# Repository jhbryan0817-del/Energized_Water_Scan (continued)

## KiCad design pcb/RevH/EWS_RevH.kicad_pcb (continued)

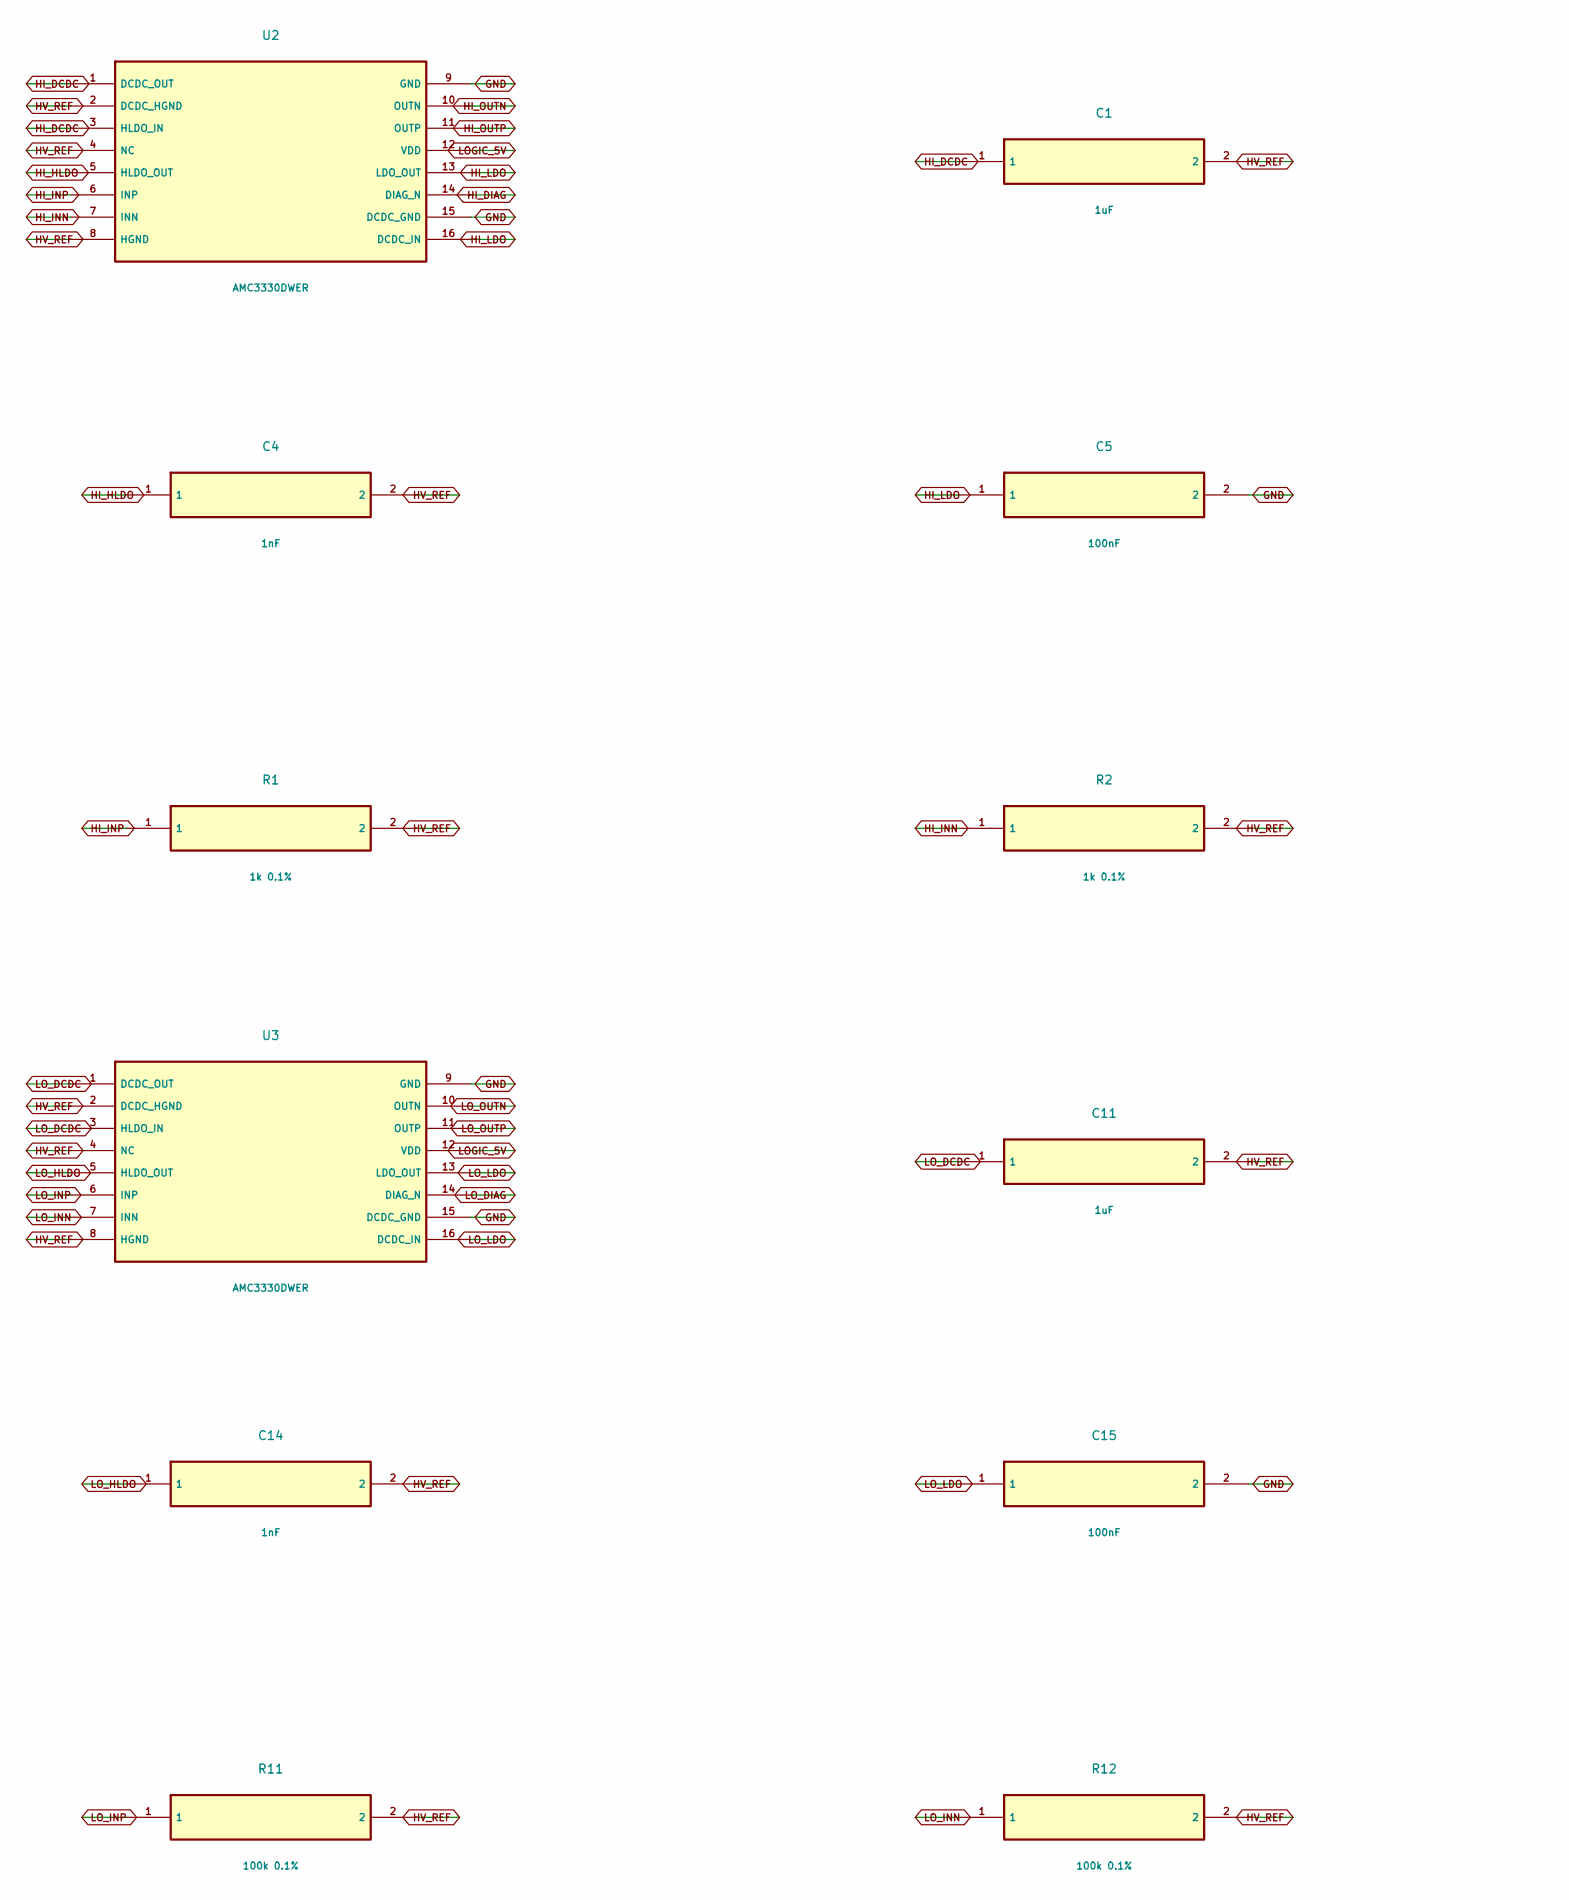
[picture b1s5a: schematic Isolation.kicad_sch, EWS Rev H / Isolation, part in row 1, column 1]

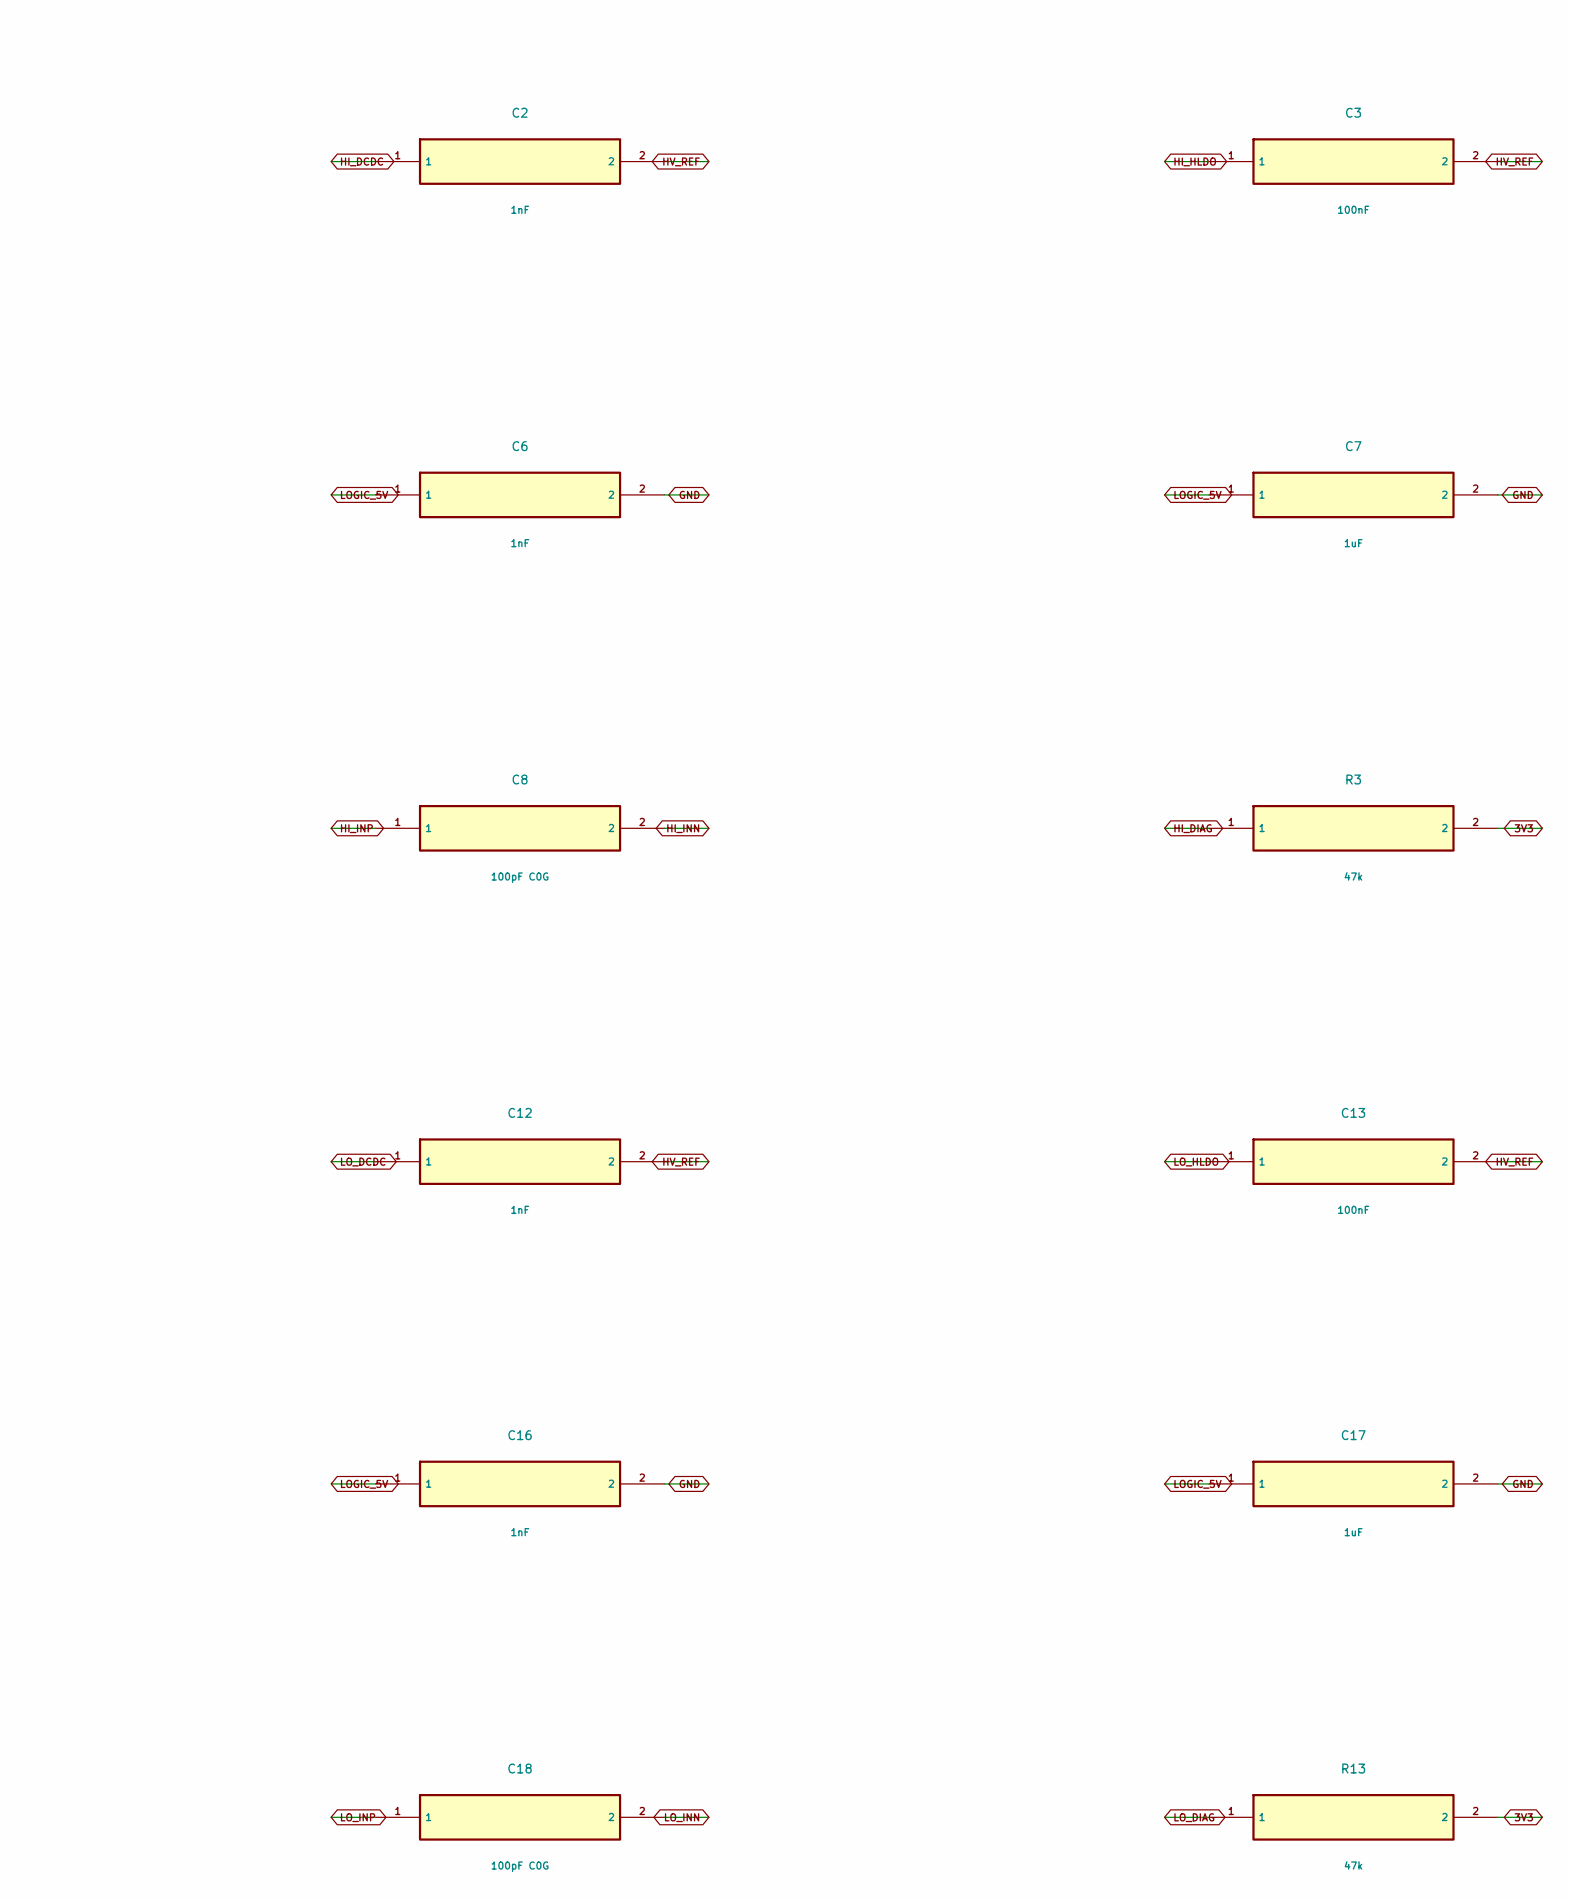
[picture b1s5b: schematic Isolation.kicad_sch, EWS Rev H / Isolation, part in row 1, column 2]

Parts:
C1: 1uF; C1
C2: 1nF; C2
C3: 100nF; C3
C4: 1nF; C4
C5: 100nF; C5
C6: 1nF; C6
C7: 1uF; C7
C8: 100pF C0G; C8
C11: 1uF; C11
C12: 1nF; C12
C13: 100nF; C13
C14: 1nF; C14
C15: 100nF; C15
C16: 1nF; C16
C17: 1uF; C17
C18: 100pF C0G; C18
R1: 1k 0.1%; R1
R2: 1k 0.1%; R2
R3: 47k; R3
R11: 100k 0.1%; R11
R12: 100k 0.1%; R12
R13: 47k; R13
U2: AMC3330DWER; U2
U3: AMC3330DWER; U3

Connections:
3V3: R3.2, R13.2; also elsewhere on the board
GND: C5.2, C6.2, C7.2, C15.2, C16.2, C17.2, U2.9 (GND), U2.15 (DCDC_GND), U3.9 (GND), U3.15 (DCDC_GND); also elsewhere on the board
HI_DCDC: C1.1, C2.1, U2.1 (DCDC_OUT), U2.3 (HLDO_IN)
HI_DIAG: R3.1, U2.14 (DIAG_N); also elsewhere on the board
HI_HLDO: C3.1, C4.1, U2.5 (HLDO_OUT)
HI_INN: C8.2, R2.1, U2.7 (INN); also elsewhere on the board
HI_INP: C8.1, R1.1, U2.6 (INP); also elsewhere on the board
HI_LDO: C5.1, U2.13 (LDO_OUT), U2.16 (DCDC_IN)
HI_OUTN: U2.10 (OUTN); also elsewhere on the board
HI_OUTP: U2.11 (OUTP); also elsewhere on the board
HV_REF: C1.2, C2.2, C3.2, C4.2, C11.2, C12.2, C13.2, C14.2, R1.2, R2.2, R11.2, R12.2, U2.2 (DCDC_HGND), U2.4 (NC), U2.8 (HGND), U3.2 (DCDC_HGND), U3.4 (NC), U3.8 (HGND); also elsewhere on the board
LOGIC_5V: C6.1, C7.1, C16.1, C17.1, U2.12 (VDD), U3.12 (VDD); also elsewhere on the board
LO_DCDC: C11.1, C12.1, U3.1 (DCDC_OUT), U3.3 (HLDO_IN)
LO_DIAG: R13.1, U3.14 (DIAG_N); also elsewhere on the board
LO_HLDO: C13.1, C14.1, U3.5 (HLDO_OUT)
LO_INN: C18.2, R12.1, U3.7 (INN); also elsewhere on the board
LO_INP: C18.1, R11.1, U3.6 (INP); also elsewhere on the board
LO_LDO: C15.1, U3.13 (LDO_OUT), U3.16 (DCDC_IN)
LO_OUTN: U3.10 (OUTN); also elsewhere on the board
LO_OUTP: U3.11 (OUTP); also elsewhere on the board

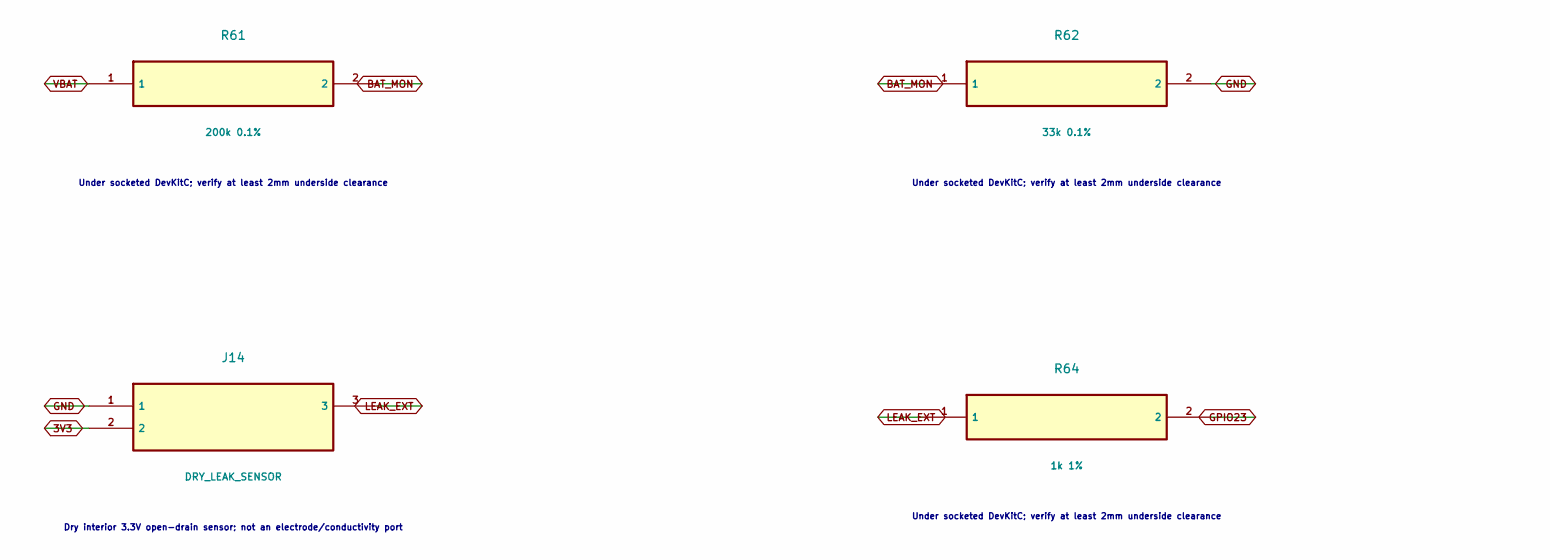
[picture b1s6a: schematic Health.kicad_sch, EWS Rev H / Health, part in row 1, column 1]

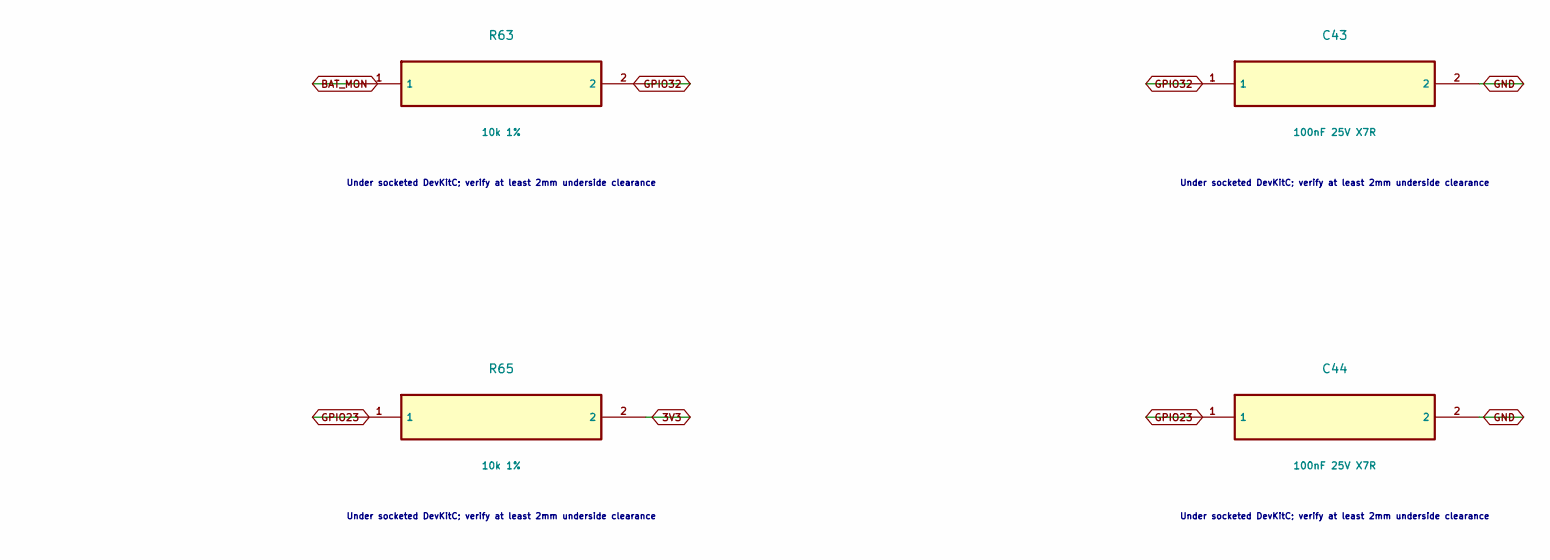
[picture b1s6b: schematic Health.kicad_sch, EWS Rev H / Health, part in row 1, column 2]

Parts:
C43: 100nF 25V X7R; C43
C44: 100nF 25V X7R; C44
J14: DRY_LEAK_SENSOR; J14
R61: 200k 0.1%; R61
R62: 33k 0.1%; R62
R63: 10k 1%; R63
R64: 1k 1%; R64
R65: 10k 1%; R65

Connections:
3V3: J14.2, R65.2; also elsewhere on the board
BAT_MON: R61.2, R62.1, R63.1
GND: C43.2, C44.2, J14.1, R62.2; also elsewhere on the board
GPIO23: C44.1, R64.2, R65.1; also elsewhere on the board
GPIO32: C43.1, R63.2; also elsewhere on the board
LEAK_EXT: J14.3, R64.1
VBAT: R61.1; also elsewhere on the board

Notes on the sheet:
Under socketed DevKitC; verify at least 2mm underside clearance
Dry interior 3.3V open-drain sensor; not an electrode/conductivity port

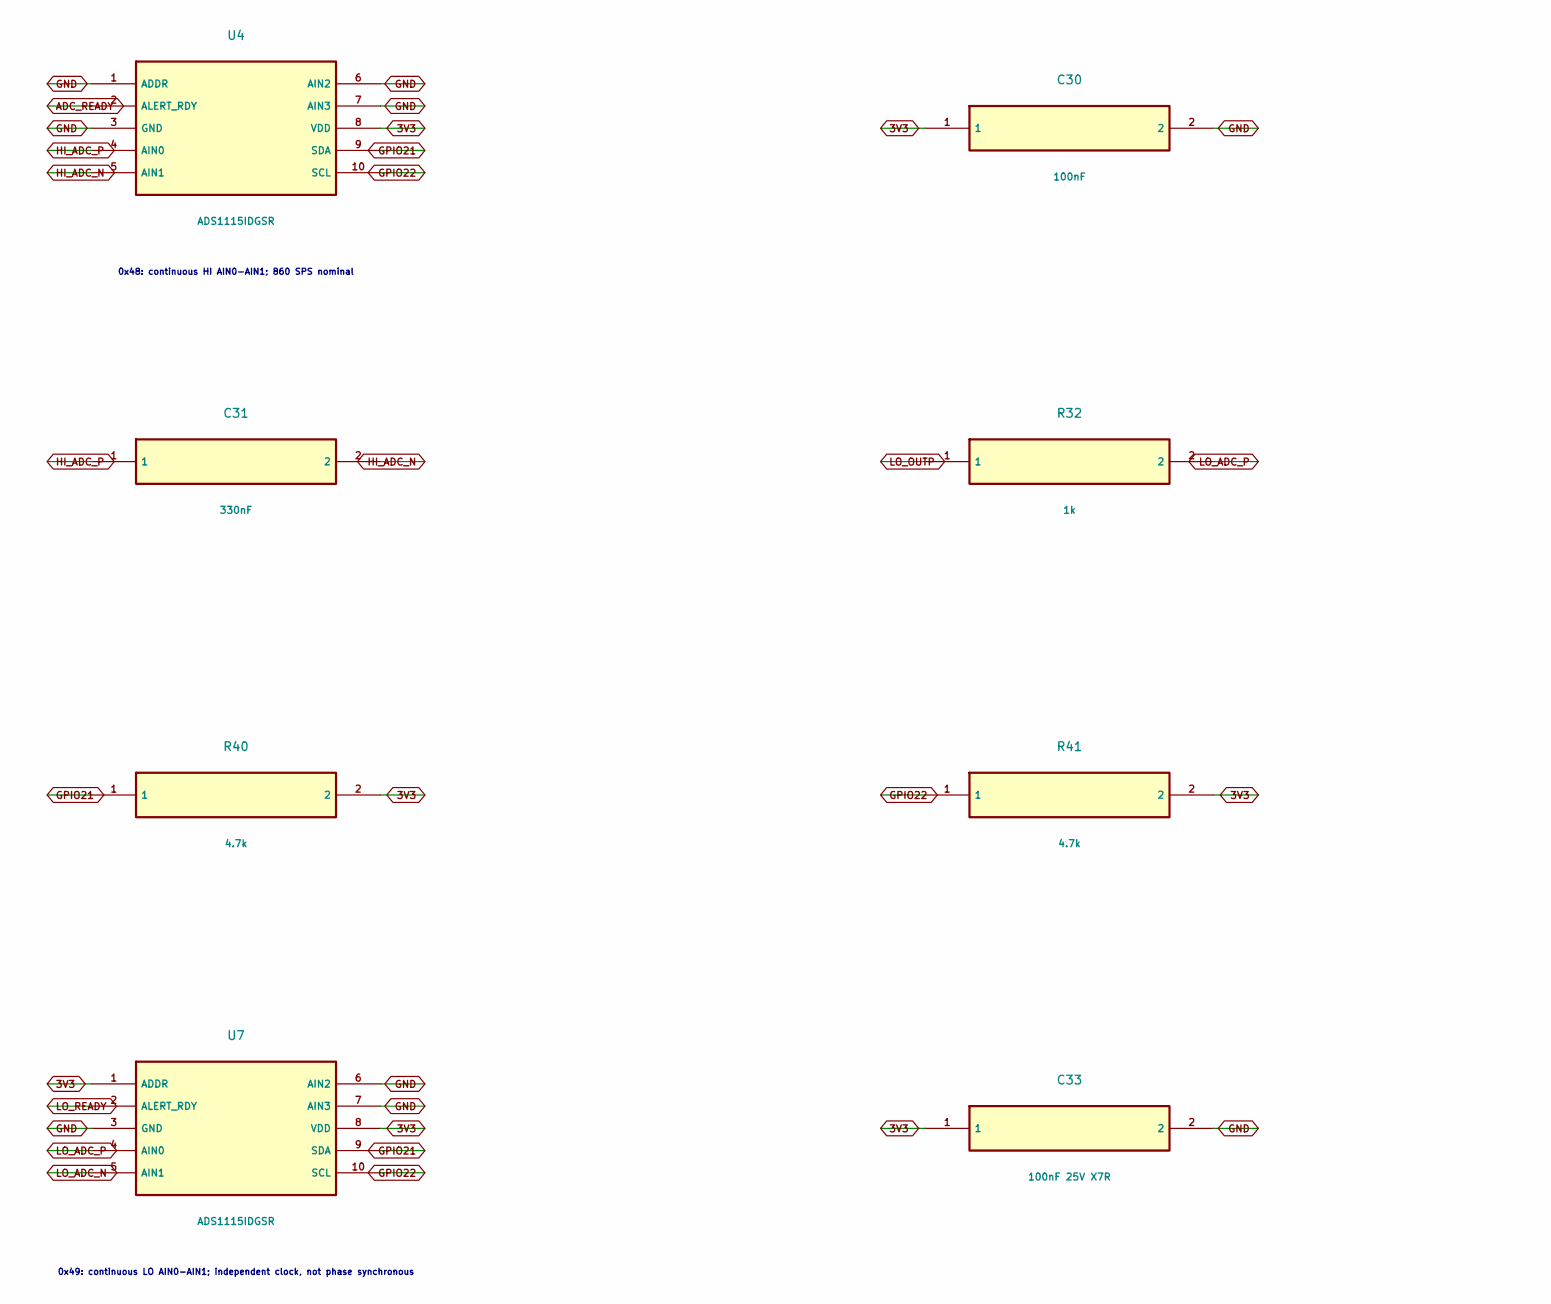
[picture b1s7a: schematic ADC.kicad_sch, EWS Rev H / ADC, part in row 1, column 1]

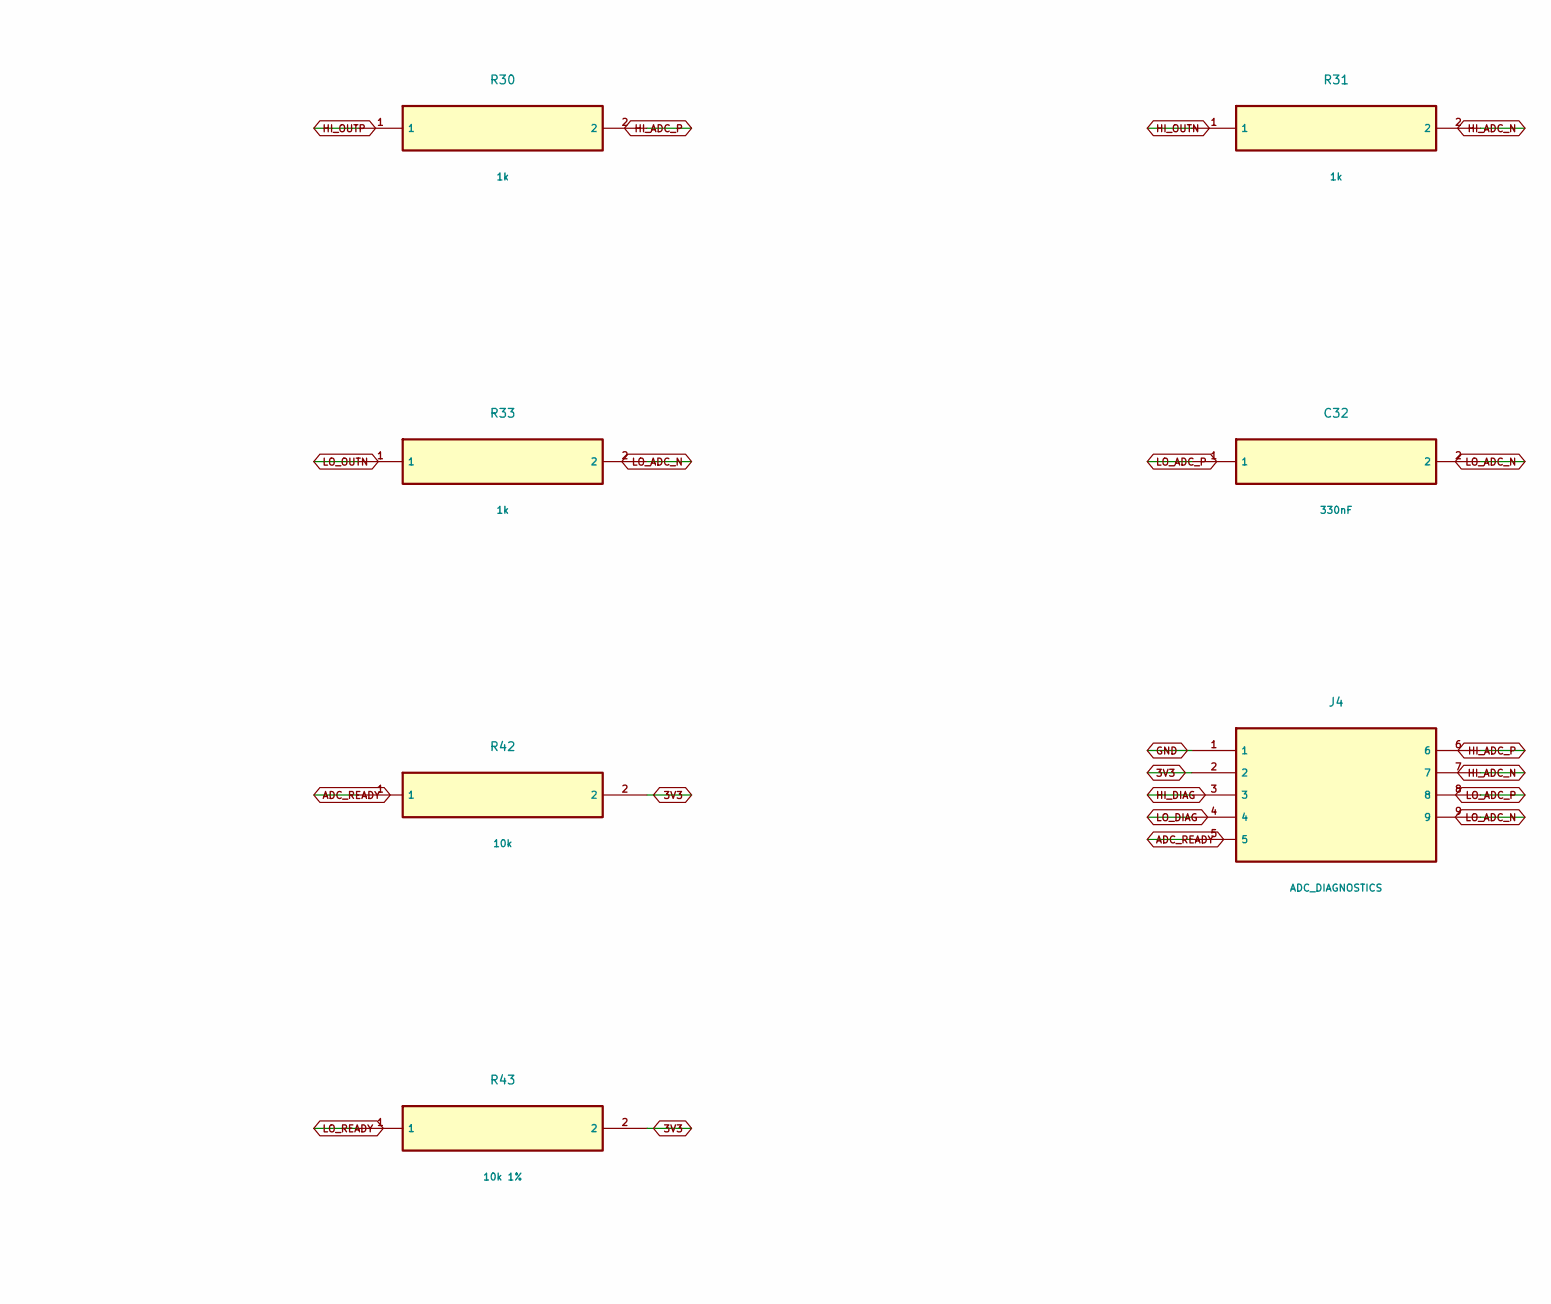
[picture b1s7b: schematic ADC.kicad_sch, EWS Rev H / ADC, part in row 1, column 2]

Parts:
C30: 100nF; C30
C31: 330nF; C31
C32: 330nF; C32
C33: 100nF 25V X7R; C33
J4: ADC_DIAGNOSTICS; J4
R30: 1k; R30
R31: 1k; R31
R32: 1k; R32
R33: 1k; R33
R40: 4.7k; R40
R41: 4.7k; R41
R42: 10k; R42
R43: 10k 1%; R43
U4: ADS1115IDGSR; U4
U7: ADS1115IDGSR; U7

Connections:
3V3: C30.1, C33.1, J4.2, R40.2, R41.2, R42.2, R43.2, U4.8 (VDD), U7.1 (ADDR), U7.8 (VDD); also elsewhere on the board
ADC_READY: J4.5, R42.1, U4.2 (ALERT_RDY); also elsewhere on the board
GND: C30.2, C33.2, J4.1, U4.1 (ADDR), U4.3 (GND), U4.6 (AIN2), U4.7 (AIN3), U7.3 (GND), U7.6 (AIN2), U7.7 (AIN3); also elsewhere on the board
GPIO21: R40.1, U4.9 (SDA), U7.9 (SDA); also elsewhere on the board
GPIO22: R41.1, U4.10 (SCL), U7.10 (SCL); also elsewhere on the board
HI_ADC_N: C31.2, J4.7, R31.2, U4.5 (AIN1)
HI_ADC_P: C31.1, J4.6, R30.2, U4.4 (AIN0)
HI_DIAG: J4.3; also elsewhere on the board
HI_OUTN: R31.1; also elsewhere on the board
HI_OUTP: R30.1; also elsewhere on the board
LO_ADC_N: C32.2, J4.9, R33.2, U7.5 (AIN1)
LO_ADC_P: C32.1, J4.8, R32.2, U7.4 (AIN0)
LO_DIAG: J4.4; also elsewhere on the board
LO_OUTN: R33.1; also elsewhere on the board
LO_OUTP: R32.1; also elsewhere on the board
LO_READY: R43.1, U7.2 (ALERT_RDY); also elsewhere on the board

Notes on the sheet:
0x48: continuous HI AIN0-AIN1; 860 SPS nominal
0x49: continuous LO AIN0-AIN1; independent clock, not phase synchronous

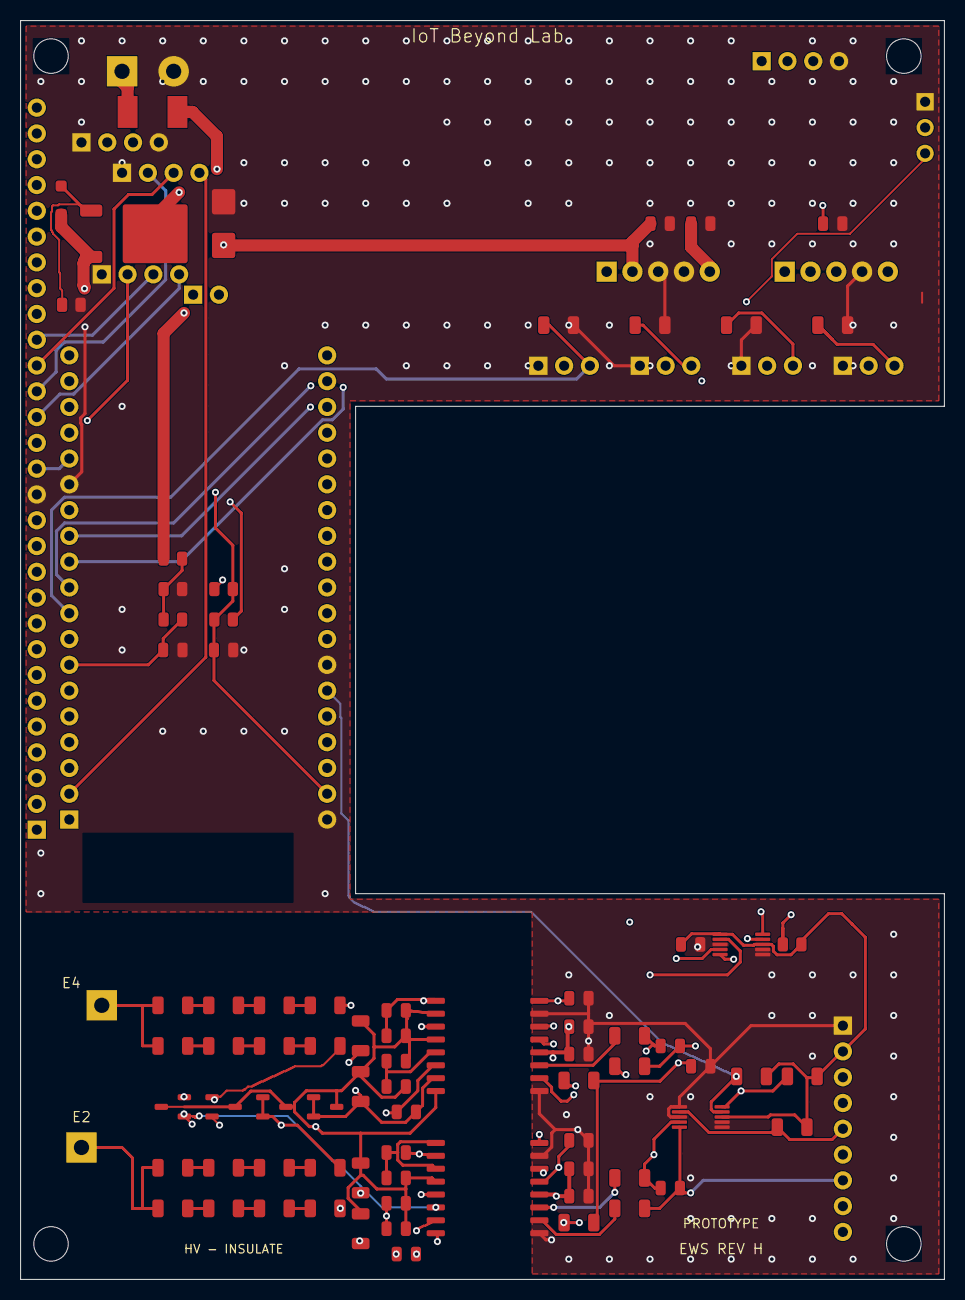
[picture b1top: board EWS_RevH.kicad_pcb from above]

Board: 6 copper layers, 91.0 x 124.0 mm, 100 parts (0 on the bottom side), 74 nets.

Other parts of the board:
H1: M3 nylon hardware; H1
H2: M3 nylon hardware; H2
H3: M3 nylon hardware; H3
H4: M3 nylon hardware; H4
M1: Hobbywing WP1625 on SJ3550; M1

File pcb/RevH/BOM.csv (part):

ref,value,mpn,footprint,note,procurement_status,source
U1,ESP32-DevKitC V4 WROOM,ESP32-DevKitC-32E,EWS:U1,WROOM DevKitC V4; confirm module/38-pin interface; two 1x19 sockets required,Selected candidate; verify exact supplier drawing and availability,https://docs.espressif.com/projects/esp-dev-kits/en/latest/e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
J1,EXPANSION_3V3_ONLY,,EWS:J1,,"HOLD: select manufacturer part against value, footprint and ratings",
J2,I2C_3V3,,EWS:J2,,"HOLD: select manufacturer part against value, footprint and ratings",
J3,UART_RESET,,EWS:J3,,"HOLD: select manufacturer part against value, footprint and ratings",
JP1,REMOVE_FOR_USB,,EWS:JP1,,"HOLD: select manufacturer part against value, footprint and ratings",
U2,AMC3330DWER,AMC3330DWER,EWS:U2,,Selected candidate; verify exact supplier drawing and availability,https://www.ti.com/lit/ds/symlink/amc3330.pdf
C1,1uF,,EWS:C1,"; 0805, >=25V; C0G for 100pF/1nF, X7R otherwise; verify effective capacitance","HOLD: select manufacturer part against value, footprint and ratings",
C2,1nF,,EWS:C2,"; 0805, >=25V; C0G for 100pF/1nF, X7R otherwise; verify effective capacitance","HOLD: select manufacturer part against value, footprint and ratings",
C3,100nF,,EWS:C3,"; 0805, >=25V; C0G for 100pF/1nF, X7R otherwise; verify effective capacitance","HOLD: select manufacturer part against value, footprint and ratings",
C4,1nF,,EWS:C4,"; 0805, >=25V; C0G for 100pF/1nF, X7R otherwise; verify effective capacitance","HOLD: select manufacturer part against value, footprint and ratings",
C5,100nF,,EWS:C5,"; 0805, >=25V; C0G for 100pF/1nF, X7R otherwise; verify effective capacitance","HOLD: select manufacturer part against value, footprint and ratings",
C6,1nF,,EWS:C6,"; 0805, >=25V; C0G for 100pF/1nF, X7R otherwise; verify effective capacitance","HOLD: select manufacturer part against value, footprint and ratings",
C7,1uF,,EWS:C7,"; 0805, >=25V; C0G for 100pF/1nF, X7R otherwise; verify effective capacitance","HOLD: select manufacturer part against value, footprint and ratings",
R1,1k 0.1%,,EWS:R1,,"HOLD: select manufacturer part against value, footprint and ratings",
R2,1k 0.1%,,EWS:R2,,"HOLD: select manufacturer part against value, footprint and ratings",
C8,100pF C0G,,EWS:C8,"; 0805, >=25V; C0G for 100pF/1nF, X7R otherwise; verify effective capacitance","HOLD: select manufacturer part against value, footprint and ratings",
R3,47k,,EWS:R3,,"HOLD: select manufacturer part against value, footprint and ratings",
R100,249k 0.1% 200V,TNPW1206249KBEEA,EWS:R100,,Selected candidate; verify exact supplier drawing and availability,https://www.vishay.com/docs/28758/tnpw_e3.pdf
R101,249k 0.1% 200V,TNPW1206249KBEEA,EWS:R101,,Selected candidate; verify exact supplier drawing and availability,https://www.vishay.com/docs/28758/tnpw_e3.pdf
R102,249k 0.1% 200V,TNPW1206249KBEEA,EWS:R102,,Selected candidate; verify exact supplier drawing and availability,https://www.vishay.com/docs/28758/tnpw_e3.pdf
R103,249k 0.1% 200V,TNPW1206249KBEEA,EWS:R103,,Selected candidate; verify exact supplier drawing and availability,https://www.vishay.com/docs/28758/tnpw_e3.pdf
R104,249k 0.1% 200V,TNPW1206249KBEEA,EWS:R104,,Selected candidate; verify exact supplier drawing and availability,https://www.vishay.com/docs/28758/tnpw_e3.pdf
R105,249k 0.1% 200V,TNPW1206249KBEEA,EWS:R105,,Selected candidate; verify exact supplier drawing and availability,https://www.vishay.com/docs/28758/tnpw_e3.pdf
R106,249k 0.1% 200V,TNPW1206249KBEEA,EWS:R106,,Selected candidate; verify exact supplier drawing and availability,https://www.vishay.com/docs/28758/tnpw_e3.pdf
R107,249k 0.1% 200V,TNPW1206249KBEEA,EWS:R107,,Selected candidate; verify exact supplier drawing and availability,https://www.vishay.com/docs/28758/tnpw_e3.pdf
D1,BAV199,"BAV199,215",EWS:D1,,Selected candidate; verify exact supplier drawing and availability,https://assets.nexperia.com/documents/data-sheet/BAV199.pdf
D2,BAV199,"BAV199,215",EWS:D2,,Selected candidate; verify exact supplier drawing and availability,https://assets.nexperia.com/documents/data-sheet/BAV199.pdf
U3,AMC3330DWER,AMC3330DWER,EWS:U3,,Selected candidate; verify exact supplier drawing and availability,https://www.ti.com/lit/ds/symlink/amc3330.pdf
C11,1uF,,EWS:C11,"; 0805, >=25V; C0G for 100pF/1nF, X7R otherwise; verify effective capacitance","HOLD: select manufacturer part against value, footprint and ratings",
C12,1nF,,EWS:C12,"; 0805, >=25V; C0G for 100pF/1nF, X7R otherwise; verify effective capacitance","HOLD: select manufacturer part against value, footprint and ratings",
C13,100nF,,EWS:C13,"; 0805, >=25V; C0G for 100pF/1nF, X7R otherwise; verify effective capacitance","HOLD: select manufacturer part against value, footprint and ratings",
C14,1nF,,EWS:C14,"; 0805, >=25V; C0G for 100pF/1nF, X7R otherwise; verify effective capacitance","HOLD: select manufacturer part against value, footprint and ratings",
C15,100nF,,EWS:C15,"; 0805, >=25V; C0G for 100pF/1nF, X7R otherwise; verify effective capacitance","HOLD: select manufacturer part against value, footprint and ratings",
C16,1nF,,EWS:C16,"; 0805, >=25V; C0G for 100pF/1nF, X7R otherwise; verify effective capacitance","HOLD: select manufacturer part against value, footprint and ratings",
C17,1uF,,EWS:C17,"; 0805, >=25V; C0G for 100pF/1nF, X7R otherwise; verify effective capacitance","HOLD: select manufacturer part against value, footprint and ratings",
R11,100k 0.1%,,EWS:R11,,"HOLD: select manufacturer part against value, footprint and ratings",
R12,100k 0.1%,,EWS:R12,,"HOLD: select manufacturer part against value, footprint and ratings",
C18,100pF C0G,,EWS:C18,"; 0805, >=25V; C0G for 100pF/1nF, X7R otherwise; verify effective capacitance","HOLD: select manufacturer part against value, footprint and ratings",
R13,47k,,EWS:R13,,"HOLD: select manufacturer part against value, footprint and ratings",
R110,249k 0.1% 200V,TNPW1206249KBEEA,EWS:R110,,Selected candidate; verify exact supplier drawing and availability,https://www.vishay.com/docs/28758/tnpw_e3.pdf
R111,249k 0.1% 200V,TNPW1206249KBEEA,EWS:R111,,Selected candidate; verify exact supplier drawing and availability,https://www.vishay.com/docs/28758/tnpw_e3.pdf
R112,249k 0.1% 200V,TNPW1206249KBEEA,EWS:R112,,Selected candidate; verify exact supplier drawing and availability,https://www.vishay.com/docs/28758/tnpw_e3.pdf
R113,249k 0.1% 200V,TNPW1206249KBEEA,EWS:R113,,Selected candidate; verify exact supplier drawing and availability,https://www.vishay.com/docs/28758/tnpw_e3.pdf
R114,249k 0.1% 200V,TNPW1206249KBEEA,EWS:R114,,Selected candidate; verify exact supplier drawing and availability,https://www.vishay.com/docs/28758/tnpw_e3.pdf
R115,249k 0.1% 200V,TNPW1206249KBEEA,EWS:R115,,Selected candidate; verify exact supplier drawing and availability,https://www.vishay.com/docs/28758/tnpw_e3.pdf
R116,249k 0.1% 200V,TNPW1206249KBEEA,EWS:R116,,Selected candidate; verify exact supplier drawing and availability,https://www.vishay.com/docs/28758/tnpw_e3.pdf
R117,249k 0.1% 200V,TNPW1206249KBEEA,EWS:R117,,Selected candidate; verify exact supplier drawing and availability,https://www.vishay.com/docs/28758/tnpw_e3.pdf
D3,BAV199,"BAV199,215",EWS:D3,,Selected candidate; verify exact supplier drawing and availability,https://assets.nexperia.com/documents/data-sheet/BAV199.pdf
D4,BAV199,"BAV199,215",EWS:D4,,Selected candidate; verify exact supplier drawing and availability,https://assets.nexperia.com/documents/data-sheet/BAV199.pdf
U4,ADS1115IDGSR,ADS1115IDGSR,EWS:U4,0x48: continuous HI AIN0-AIN1; 860 SPS nominal,Selected candidate; verify exact supplier drawing and availability,https://www.ti.com/lit/ds/symlink/ads1115.pdf
C30,100nF,,EWS:C30,"; 0805, >=25V; C0G for 100pF/1nF, X7R otherwise; verify effective capacitance","HOLD: select manufacturer part against value, footprint and ratings",
R30,1k,,EWS:R30,,"HOLD: select manufacturer part against value, footprint and ratings",
R31,1k,,EWS:R31,,"HOLD: select manufacturer part against value, footprint and ratings",
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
